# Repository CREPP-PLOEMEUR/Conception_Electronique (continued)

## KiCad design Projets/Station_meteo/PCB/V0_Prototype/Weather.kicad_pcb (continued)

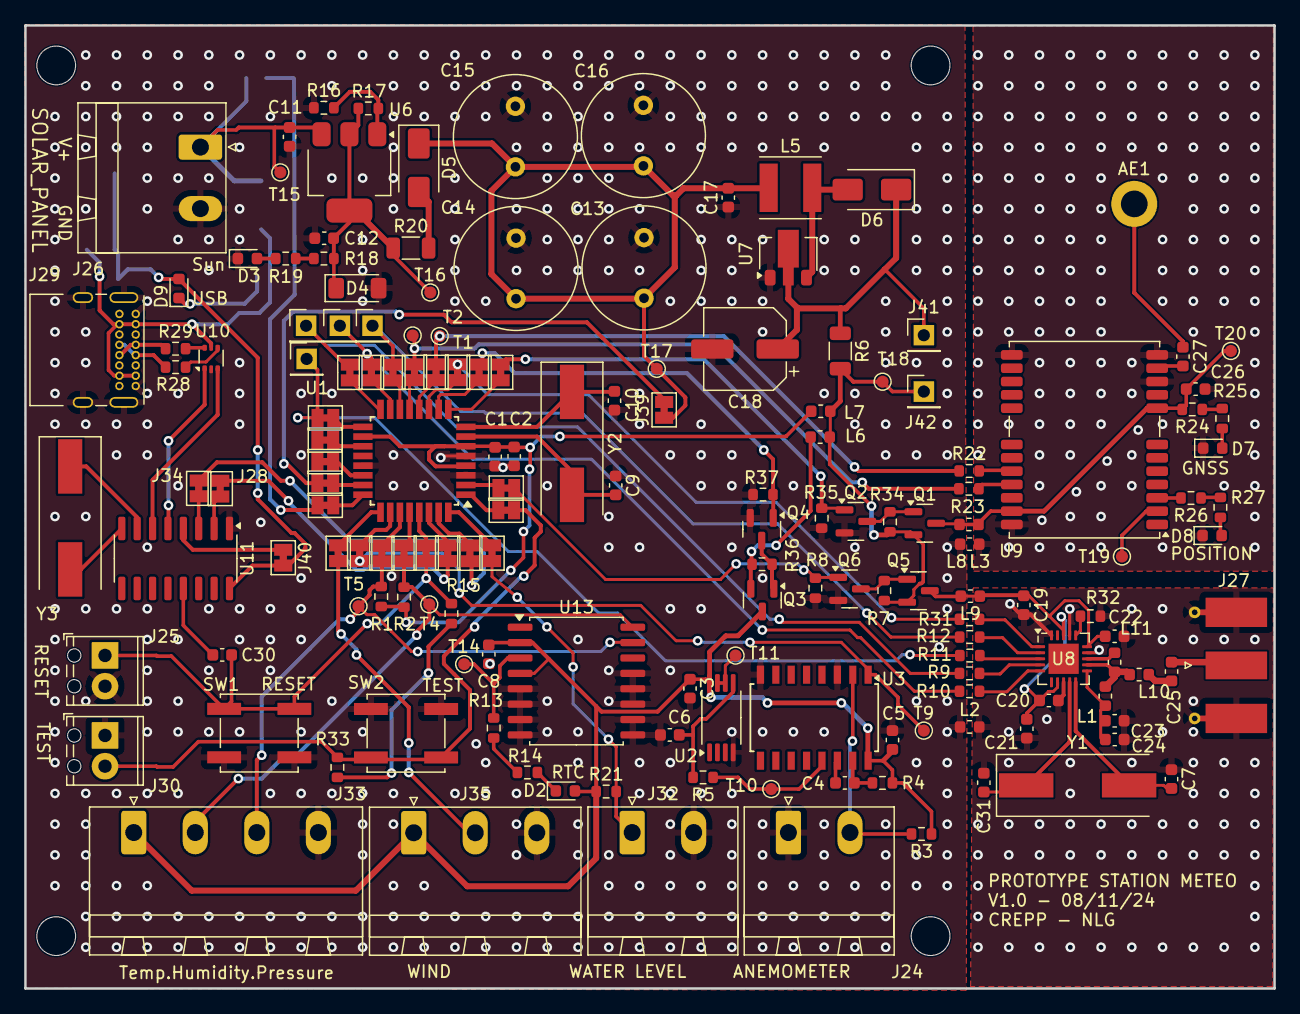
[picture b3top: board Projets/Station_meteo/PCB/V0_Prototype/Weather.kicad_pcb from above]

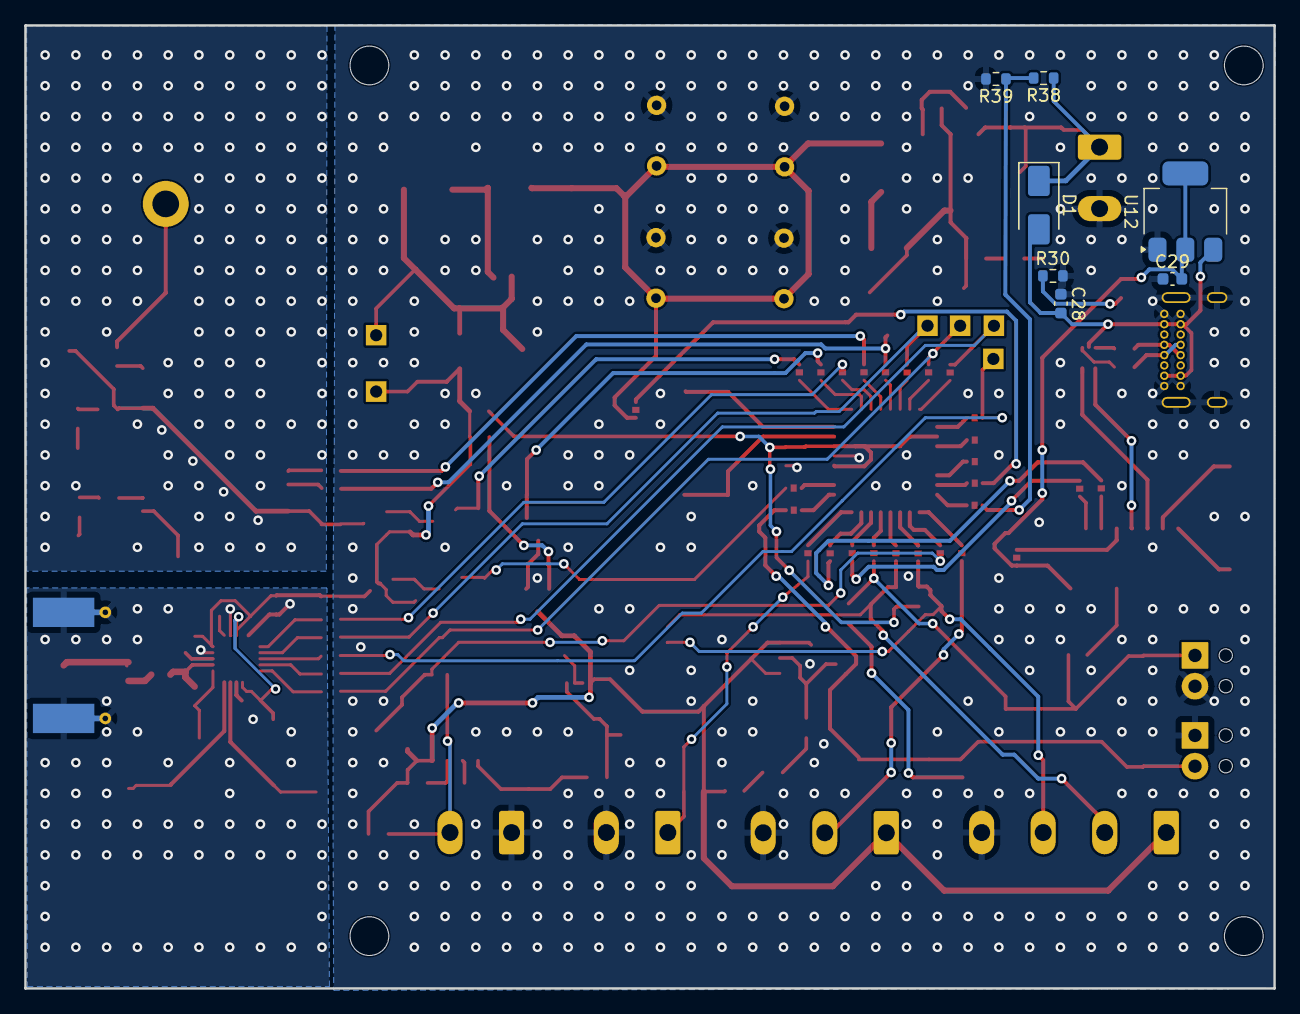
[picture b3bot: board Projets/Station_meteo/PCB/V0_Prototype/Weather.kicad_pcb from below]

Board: 2 copper layers, 103.1 x 79.5 mm, 172 parts (7 on the bottom side), 115 nets.

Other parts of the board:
C7, C31: 22pF; C_0603_1608Metric
D1: SS24; D_SMA
J30: KF128-2.54_2P; TerminalBlock_Phoenix_MPT-0,5-2-2.54_1x02_P2.54mm_Horizontal
J41, J42: Conn_01x01_Pin; PinHeader_1x01_P2.54mm_Vertical
R33: 10k; R_0603_1608Metric
R38, R39: 100k; R_0603_1608Metric
SW2: PB_SMD_12V_50MA_6MM_6MM; SW_Push_1P1T_NO_CK_KSC7xxJ
Y1: 16MHz; Crystal_SMD_HC49-SD

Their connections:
/+3.3V_MCU: R33.1; also elsewhere on the board
/+5V_USB: D1.2 (A); also elsewhere on the board
/MCU/PC1-A1: R38.2, R39.1; also elsewhere on the board
/MCU/PD3-D3-(INT1)~: J30.2, R33.2, SW2.2 (B); also elsewhere on the board
/NRF24/XTAL1/XTAl_1: C7.2, Y1.2; also elsewhere on the board
/NRF24/XTAL1/XTAl_2: C31.2, Y1.1; also elsewhere on the board
/Power/+3.3V: J41.1; also elsewhere on the board
/Power/+3.3V_RF: J42.1; also elsewhere on the board
GND: J30.1, R39.2, SW2.1 (A); also elsewhere on the board
GND_RF: C7.1, C31.1; also elsewhere on the board
unnamed 44: D1.1 (K), R38.1; also elsewhere on the board

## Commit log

2024-10-13 Add initial file
2024-10-26 Add files
2024-10-27 Add diagramm
2024-11-03 Add schematic and PCBA
2024-11-04 Update PCB
2024-11-05 Add shcematic file
2024-11-11 Add V1 THT version
2024-11-30 Update PCB_V1
2024-12-19 Add shields
2025-01-19 update of directory
2025-01-21 Update PCB Base
2025-01-25 Add vscode extension
2025-01-26 Update Weather station
2025-02-21 Update Base
2025-03-15 Update Schematic
